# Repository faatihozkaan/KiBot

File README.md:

<h1 align="center">KiBoard</h1>

<p align="center" width="100%">
  
</p>

***

<p align="center">
  
&nbsp; &nbsp; &nbsp; &nbsp;
  
</p>

***

## SPECIFICATIONS

| Parameter | Value | 
| --- | --- |
| Dimensions | 25.6 × 41.8 mm |

***

## DIRECTORY STRUCTURE

    .
    ├─ Computations       # Misc calculations
    ├─ HTML               # HTML files for generated webpage
    ├─ Images             # Pictures and renders
    │
    ├─ kibot_resources    # External resources for KiBot
    │  ├─ colors          # Color theme for KiCad
    │  ├─ fonts           # Fonts used in the project
    │  ├─ scripts         # External scripts used with KiBot
    │  └─ templates       # Templates for KiBot generated reports
    │
    ├─ kibot_yaml         # KiBot YAML config files
    ├─ KiRI               # KiRI (PCB diff viewer) files
    │
    ├─ lib                # KiCad footprint and symbol libraries
    │  ├─ 3d_models       # Component 3D models
    │  ├─ lib_fp          # Footprint libraries
    │  └─ lib_sym         # Symbol libraries
    │
    ├─ Logos              # Logos
    │
    ├─ Manufacturing      # Assembly and fabrication documents
    │  ├─ Assembly        # Assembly documents (BoM, pos, notes)
    │  │
    │  └─ Fabrication     # Fabrication documents (ZIP, notes)
    │     ├─ Drill Tables # CSV drill tables
    │     └─ Gerbers      # Gerbers
    │
    ├─ Report             # Reports for ERC/DRC
    ├─ Schematic          # PDF of schematic
    ├─ Templates          # Title block templates
    ├─ Testing
    │  └─ Testpoints      # Testpoints tables      
    │
    └─ Variants           # Outputs for assembly variants

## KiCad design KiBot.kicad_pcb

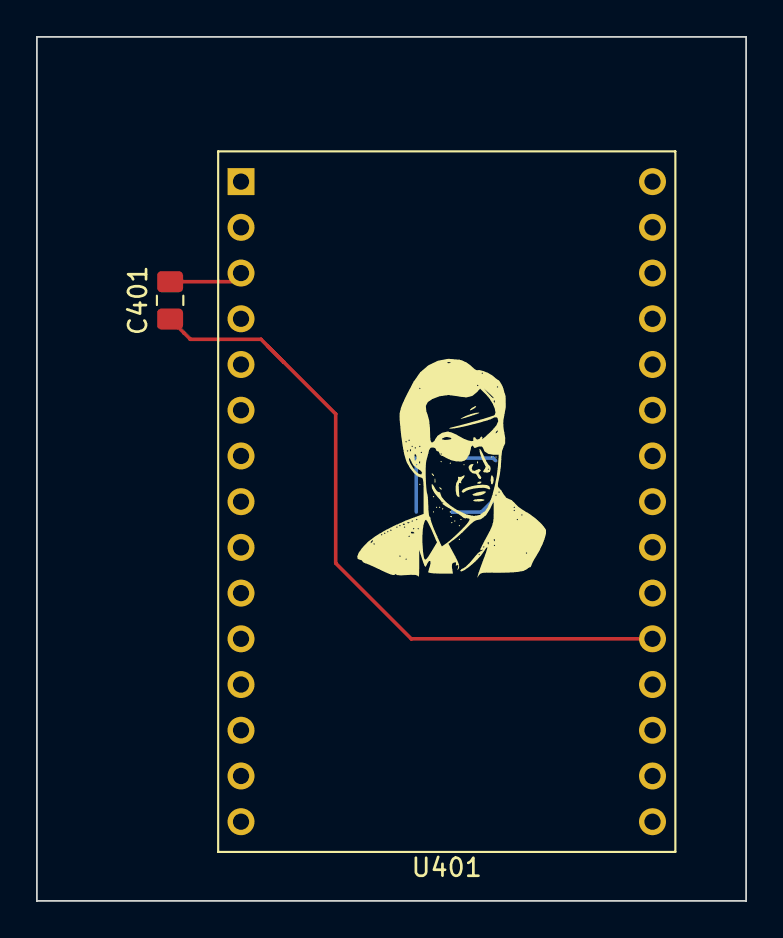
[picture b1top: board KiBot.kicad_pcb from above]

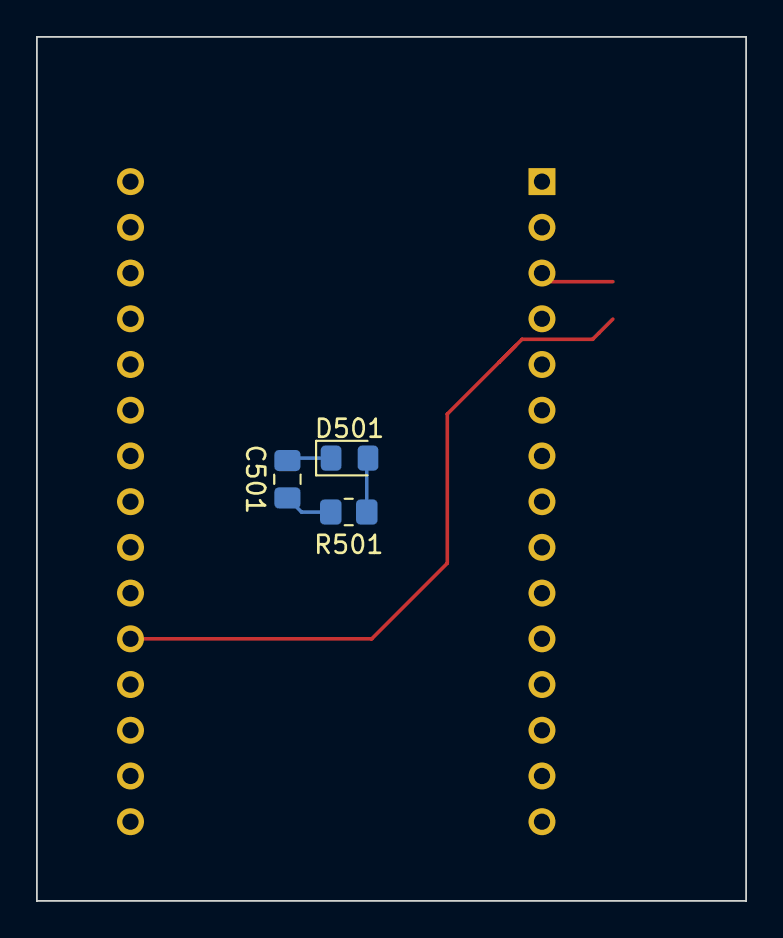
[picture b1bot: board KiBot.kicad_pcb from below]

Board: 6 copper layers, 39.4 x 48.0 mm, 5 parts (3 on the bottom side), 5 nets.

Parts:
C401, C501: C; C_0805_2012Metric_Pad1.18x1.45mm_HandSolder
D501: LED; LED_0805_2012Metric_Pad1.15x1.40mm_HandSolder
R501: R; R_0805_2012Metric_Pad1.20x1.40mm_HandSolder
U401: ESP32-C3-DevKitM-1

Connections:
unnamed: C401.1, U401.2 (3V3), U401.3 (3V3)
unnamed: C501.2, R501.1
unnamed: D501.2 (A), R501.2
unnamed: C501.1, D501.1 (K)
unnamed: C401.2, U401.20 (IO4)

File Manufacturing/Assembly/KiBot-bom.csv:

Row,Quantity Per PCB,References,Value,Datasheet,Footprint,Description,Manufacturer,Manufacturer Part Number,Supplier Part Number
1,2,C401 C501,C,~,C_0805_2012Metric_Pad1.18x1.45mm_HandSolder,Unpolarized capacitor,,,
2,1,D501,LED,~,LED_0805_2012Metric_Pad1.15x1.40mm_HandSolder,Light emitting diode,,,
3,1,R501,R,~,R_0805_2012Metric_Pad1.20x1.40mm_HandSolder,Resistor,,,
4,1,U401,ESP32-C3-DevKitM-1,https://docs.espressif.com/projects/esp-idf/en/latest/esp32c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,ESP32-C3-DevKitM-1,Development board featuring ESP32-C3-MINI-1 module,,,

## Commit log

2026-03-18 first attempt
2026-03-18 Update Outputs
2026-03-18 second update
2026-03-18 footprint added
2026-03-18 [Preliminary] Pcb layout added
2026-03-18 [CHECKED] Last check complated
2026-03-18 [CHECKED] Added a Revision History
2026-03-18 bugs fixed
2026-03-18 Update CHANGELOG
2026-03-18 Update Outputs (release)
2026-03-18 bugs fixed v2
2026-04-01 bugs fixed v3
2026-04-01 release deneme 1.0.2
2026-04-01 release deneme 1.0.3
